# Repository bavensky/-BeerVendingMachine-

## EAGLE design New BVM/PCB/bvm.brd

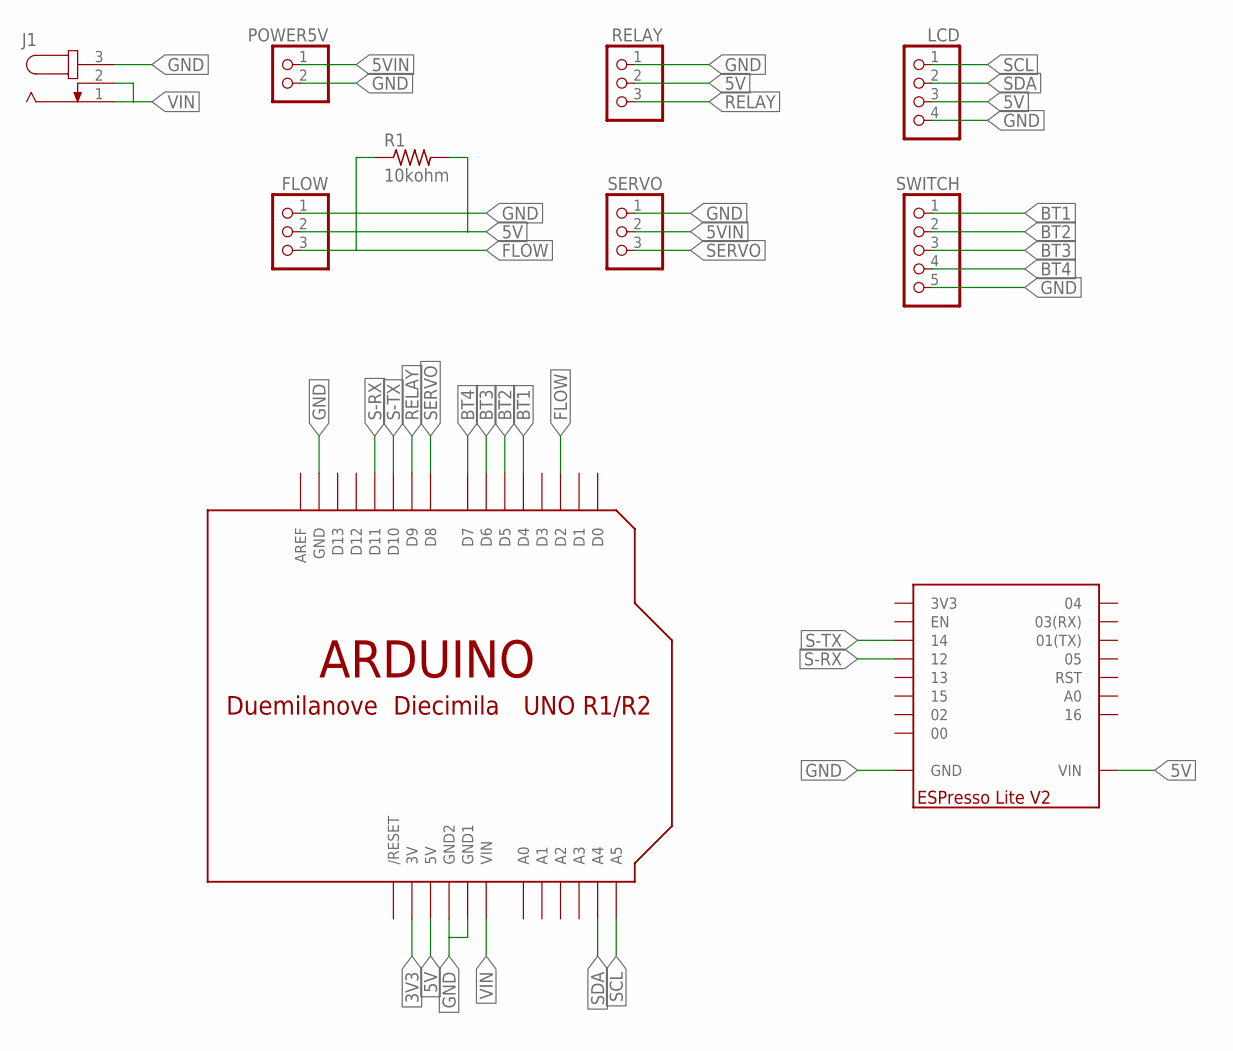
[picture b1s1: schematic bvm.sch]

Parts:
FLOW: PINHD-1X3; 1X03
J1: JACK-PLUG0; SPC4077
LCD: PINHD-1X4; 1X04
POWER5V: PINHD-1X2; 1X02
R1: 10kohm; 0207/10
RELAY: PINHD-1X3; 1X03
SERVO: PINHD-1X3; 1X03
SWITCH: PINHD-1X5; 1X05
U$1: ARDUINOUNO; ARDUINO
U$2: ESPRESSO-LITE-V2

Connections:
3V3: U$1.3V
5V: FLOW.2, LCD.3, R1.2, RELAY.2, U$1.5V, U$2.VIN1 (VIN), U$2.VIN2 (VIN)
5VIN: POWER5V.1, SERVO.2
BT1: SWITCH.1, U$1.D4
BT2: SWITCH.2, U$1.D5
BT3: SWITCH.3, U$1.D6
BT4: SWITCH.4, U$1.D7
FLOW: FLOW.3, R1.1, U$1.D2
GND: FLOW.1, J1.3, LCD.4, POWER5V.2, RELAY.1, SERVO.1, SWITCH.5, U$1.GND, U$1.GND1, U$1.GND2, U$2.GND1 (GND), U$2.GND2 (GND), U$2.GND3 (GND)
RELAY: RELAY.3, U$1.D9
S-RX: U$1.D11, U$2.12
S-TX: U$1.D10, U$2.14
SCL: LCD.1, U$1.A5
SDA: LCD.2, U$1.A4
SERVO: SERVO.3, U$1.D8
VIN: J1.1, J1.2, U$1.VIN

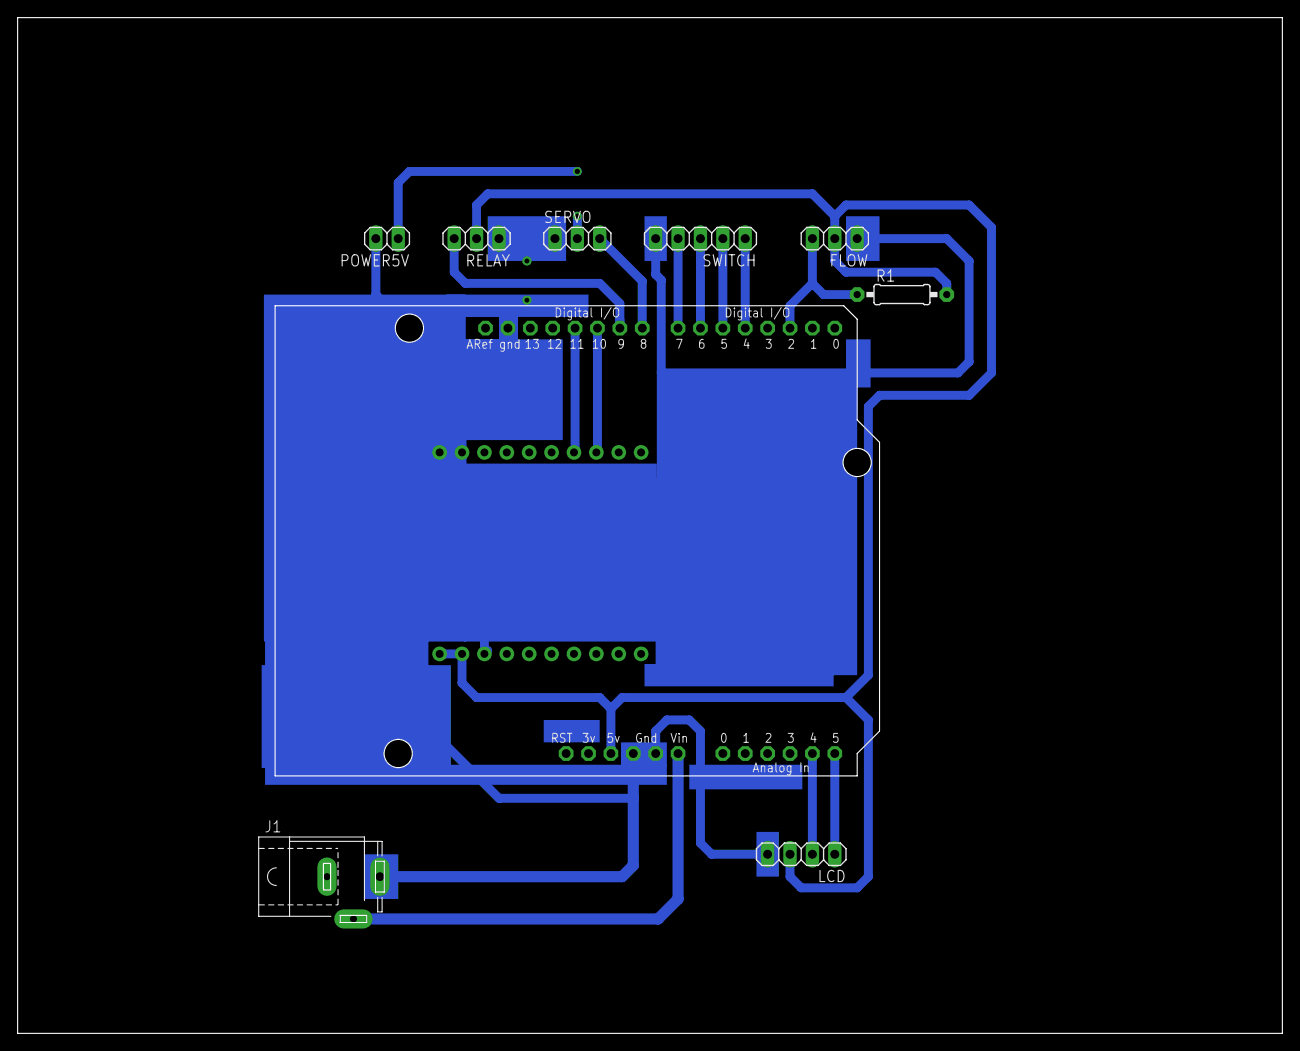
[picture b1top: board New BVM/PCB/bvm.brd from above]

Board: 2 copper layers, 143.5 x 115.2 mm, 10 parts (0 on the bottom side), 15 nets.

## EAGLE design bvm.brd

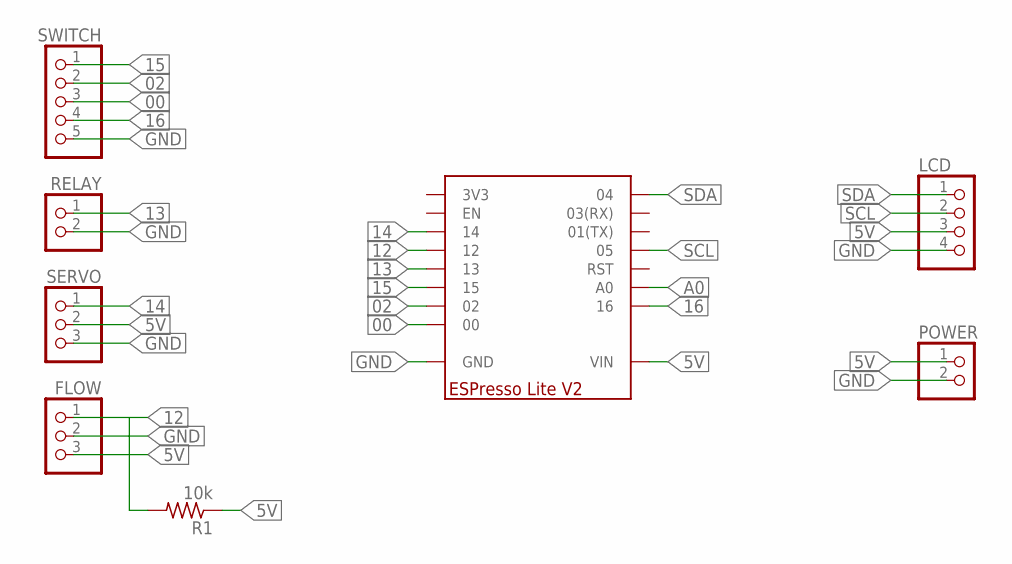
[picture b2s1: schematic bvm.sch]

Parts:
FLOW: PINHD-1X3; 1X03
LCD: PINHD-1X4; 1X04
POWER: PINHD-1X2; 1X02
R1: 10k; 0207/10
RELAY: PINHD-1X2; 1X02
SERVO: PINHD-1X3; 1X03
SWITCH: PINHD-1X5; 1X05
U$1: ESPRESSO-LITE-V2

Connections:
00: SWITCH.3, U$1.00
02: SWITCH.2, U$1.02
5V: FLOW.3, LCD.3, POWER.1, R1.1, SERVO.2, U$1.VIN1 (VIN), U$1.VIN2 (VIN)
12: FLOW.1, R1.2, U$1.12
13: RELAY.1, U$1.13
14: SERVO.1, U$1.14
15: SWITCH.1, U$1.15
16: SWITCH.4, U$1.16
A0: U$1.AO (A0)
GND: FLOW.2, LCD.4, POWER.2, RELAY.2, SERVO.3, SWITCH.5, U$1.GND1 (GND), U$1.GND2 (GND), U$1.GND3 (GND)
SCL: LCD.2, U$1.05
SDA: LCD.1, U$1.04

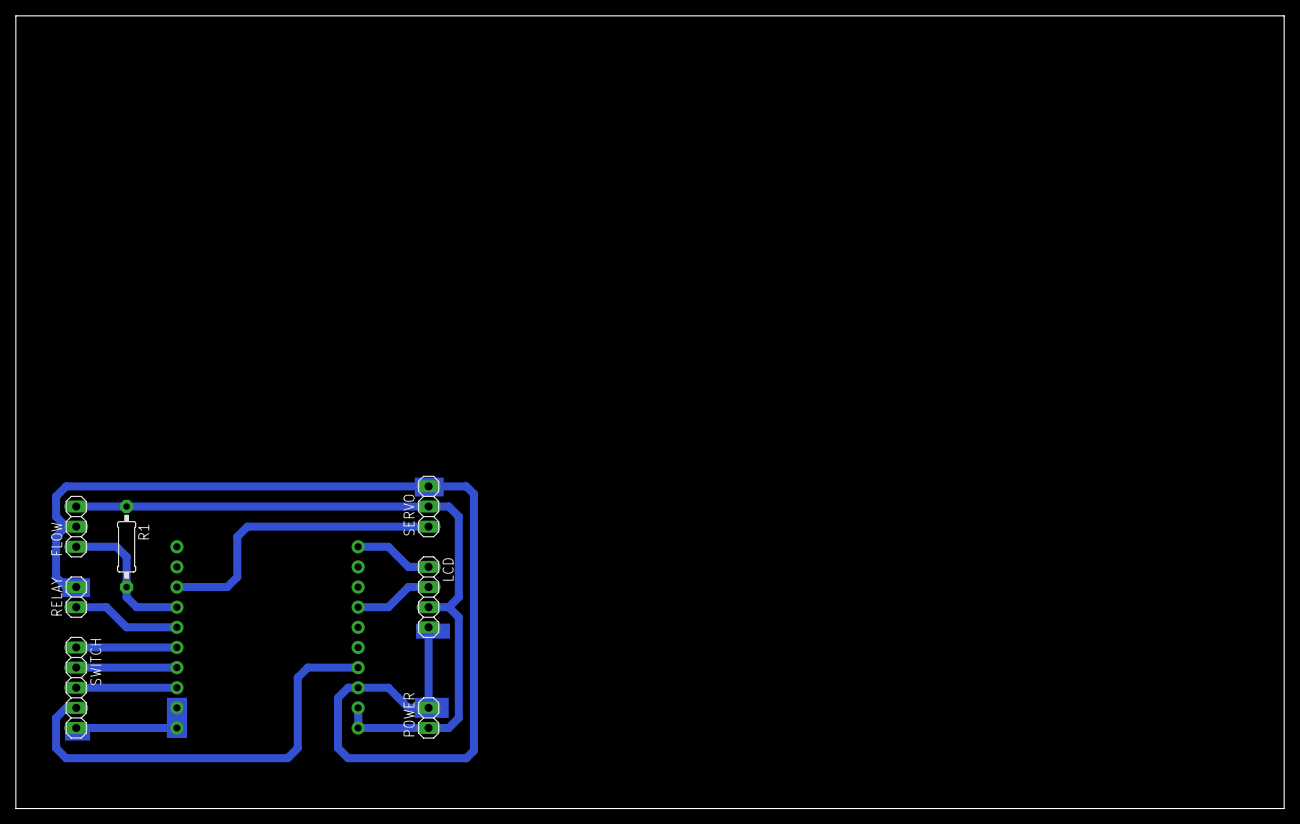
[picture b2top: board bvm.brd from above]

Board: 2 copper layers, 160.0 x 100.0 mm, 8 parts (0 on the bottom side), 11 nets.

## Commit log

2017-07-18 first code : esp8266 connected to lcd 20x4 i2c and 4 button
2017-10-08 schematic and circuit board
2017-10-08 update thingspeak 4 field
2017-12-07 update code : change board to arduino UNO
2018-01-21 update code : 2 arduino ide communication with json
2018-01-22 update : add pinout and add httpGET
2018-01-23 add scehematic
2018-01-27 add 2 button
2018-01-28 update code
2018-01-30 back to basic
2018-03-27 edit code : count value beer using delay
2018-03-27 update add Json buffer
2018-03-27 complete Json parse
2018-03-28 add default beer litre
2018-04-25 add clear stock beer
2018-10-07 change servo type
